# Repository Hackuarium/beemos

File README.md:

# BeeMoS - honey Bee Monitoring System<br/> (under development)

_[Lire en français](README.fr.md)_

The BeeMoS project is an open source bee hive monitoring system developed at the open science lab [Hackuarium](http://www.hackuarium.ch), Route de Crochy 20, Ecublens, Switzerland.

Please fee free to [contact us](https://form.jotformeu.com/71600609780354) if you would like more information.

# Objectives

Build and program an open source bee monitoring system capable of the following objectives:

- [x] Track the activity of the hives to study the behaviour of bees and monitor their health.
- [x] Track changes in the hive's weight over time to detect sudden and gradual changes (swarming, honey production ...).
- [x] Measures environmental variables including temperature, humidity, light and atmospheric pressure and study their effect on the bees.
- [ ] Send the data to a remote server for analysis, visualization or to notify the user if something unusual happens.

# Cloning the project

This project uses SUBMODULES

In order to clone use:

`git clone --recurse-submodules https://github.com/hackuarium/beemos`

To update the submodules, enter the folder you created ("beemos") and use:

`git submodule update --recursive --remote`

# Modules

To achieve the above objectives, the project follows a modular design with different hardware components. We use the I2C protocol to make modulles (i.e the boards) communicate to each other while using RJ-12 connectors in order to allow easy plugging/deplugging of different modules.

[**Counter**](counter-i2c/README.md): Counts bees entering and exiting the hive over time using infrared (IR) sensors. Each sensor consists in an IR emitter-receiver, the passage of a bee under the sensor modifies the reflected IR signal. A pair of IR sensors is used for each tunnel so that the direction of bees (i.e. entering or exiting the hive) can be determined.

Here is the orientation of the IR sensors at the back of the PCB. Be careful, the orientation of the Eagle file is seen from the top of the PCB.

[**Scale**](scale-i2c/README.md): Weighs the hive periodically using 4 load cells in Wheatstone bridge configuration.

[**Weather station**](weather-i2c/README.md): Monitors temperature, humidity, atmospheric pressure and luminosity outside of the hives.

[**Master board**](master/README.md): Communicates with all other devices over I2C, log data in memory and sends the data to a remote server. Can also track temperature inside the hive.

[**Simple master**](master-simple/README.md): A simple master board with I2C RJ-12 socket to
make some tests.

# State of the project

We have designed and ordered PCBs for the bee counter, weather station, scale and master boards. These four boards have been assembled and programmed. We also built a laser cut wooden enclosure which contains the bee counter PCB. It includes 8 individual gates that the bees use to enter/exit the hive and an upper compartment for the board so that sensor are on top of entering bees. A few field trials were launched to assess the accuracy of the bee counter but we still need to fix some things in the hardware and software to get it working (we detect false positives at the beginning and the end of sunny days, possibly due to sun beams entering and being counted as a passing bee). Similarly we need to further test the scale in order to confirm that measures are stable over long periods of time. 
Clara has joined the BeeMoS team in the summer of 2018 to make some tests of the bee counter in a controlled setting with live bees (transparent box with the beecounter inside and a camera to record video of entering/exiting bees that was compared to the readings from the board) and also participated in building a hive scale. 

The weather board can now show temperature, humidity, atmospheric pressure and relative light intensity. The scale board v1.0 has been soldered, a minor fix was needed to get it to work. The next steps will be to get the bee counter to work accurately by performing controlled tests, to assess the accuracy of the scale over time and to be able to send data wirelessly, integrate them to a database and plot them in an attractive way. 

We have assembled a complete kit, containing:
- 1 master board
- 1 counter board
- 1 scale board
- 1 weather board (to be protected from rain in a transparent container that lets the light through as well as an entry for the humidity to be accurately measured)
- 1 Si7021 humidity sensor
- 1 solar panel
- 2 temperature sensors (one wire DS18B20)
- 3 cables (RJ11 connectors)
- 1 battery 3.7V, 6600mA/h
- 1 wooden counter box
- 1 plastic box (to protect the master and scale boards from rain)
Here is what the kit actually looks like:

We already have assembled and tested some parts of it (the master, weight and weather boards in particular), but on an empty hive. The master board seems to log correctly and we are able to read the logs afterwards. Some things need to be fixed, for example sometimes the master board stops recording for long periods of time. It seems that this happens when the cables between boards (I2C interface) are too long. Since the 2G network will soon disappear in Switzerland, the SIM800L module will become useless (does not work with 3G and above). We are now (in October 2019) designing a new master board based on the ESP32 in order to be less limited in programming it (less memory limitations than for Atmega32u4-based boards) and also to have integrated WiFi and Bluetooth and possibly LoRa too for wireless communications. Since all the other boards are based on I2C communication, they should be easy to integrate with the new master board. Our current work related to ESP-32 can be found at https://github.com/Hackuarium/esp-32wroom (not tested yet).

# Further resources 

All codes, PCB board and schematic files and documentation can be found on the [BeeMoS github repository](https://github.com/Hackuarium/beemos) (in english only)

View this project on [CADLAB.io](https://cadlab.io/project/1029)

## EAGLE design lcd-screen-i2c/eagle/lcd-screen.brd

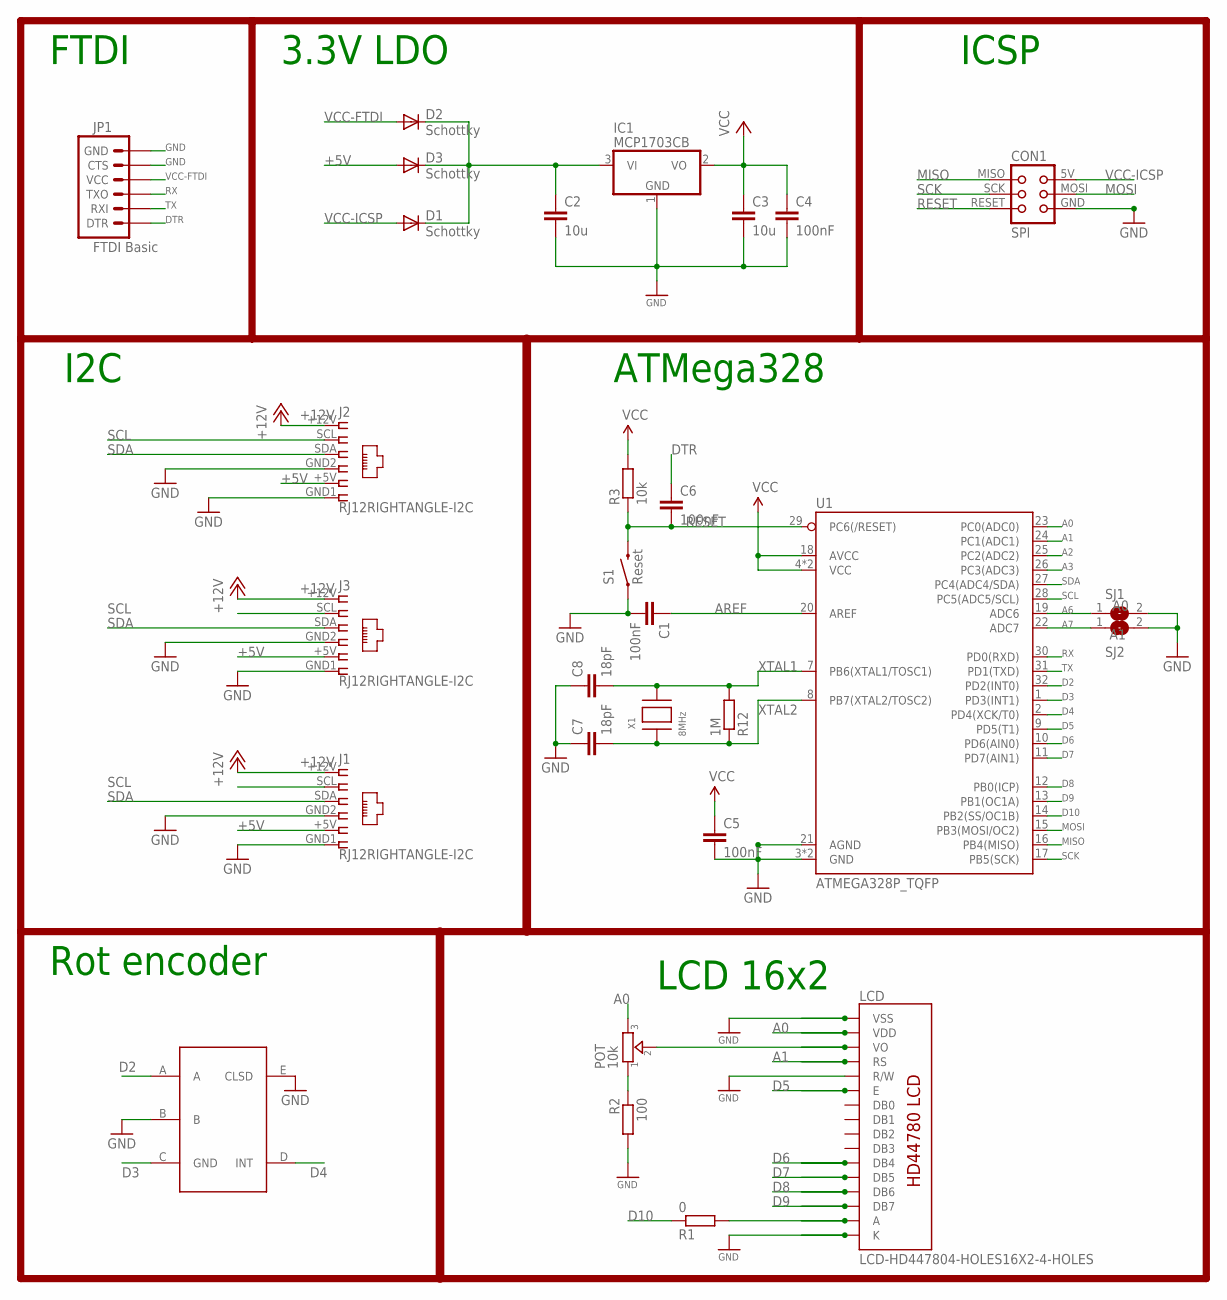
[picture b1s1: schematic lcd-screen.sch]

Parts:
C1, C4, C5, C6: 100nF; C0805K; MPN 80-C1206C104K5R; LCSC C49678
C2, C3: 10u; C0805K; MPN 77-VJ1206V106ZXQTBC; LCSC C15850
C7, C8: 18pF; C0805K; MPN 77-VJ1206A180JXXPBC; LCSC C1797
CON1: SPI; TC2030-MCP
D1, D2, D3: Schottky; SOD123; MPN 621-1N5819HW-F; LCSC C82544
IC1: MCP1703CB; SOT23; LCSC C53352
J1, J2, J3: RJ12RIGHTANGLE-I2C; RJ12-RIGHTANGLE-I2C
JP1: FTDI Basic; 1X06
LCD: LCD-HD447804-HOLES16X2-4-HOLES; LCD-16X2-4HOLES
POT: 10k; TRIMMER_3362P
R1: 0; R0805; LCSC C17477
R2: 100; R0805; LCSC C17408
R3: 10k; R0805; LCSC C17513
R12: 1M; R0805; LCSC C17514
S1: Reset; TACTILE-SWITCH-SMD-ALT01
SJ1: A0; SJ
SJ2: A1; SJ
U1: ATMEGA328P_TQFP; TQFP32-08
U$1: EC11E
X1: 8MHz; NX6035; MPN 729-F60800010; LCSC C122522

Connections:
+5V: D3.A, J1.+5V (5), J2.+5V (5), J3.+5V (5)
+12V: J1.+12V (1), J2.+12V (1), J3.+12V (1)
+XV: C2.1, D1.C, D2.C, D3.C, IC1.3 (VI)
A0: LCD.2 (VDD), POT.3, U1.23 (PC0(ADC0))
A1: LCD.4 (RS), U1.24 (PC1(ADC1))
A2: U1.25 (PC2(ADC2))
A3: U1.26 (PC3(ADC3))
A6: SJ1.1, U1.19 (ADC6)
A7: SJ2.1, U1.22 (ADC7)
AREF: C1.1, U1.20 (AREF)
D2: U1.32 (PD2(INT0)), U$1.A
D3: U1.1 (PD3(INT1)), U$1.C (GND)
D4: U1.2 (PD4(XCK/T0)), U$1.D (INT)
D5: LCD.6 (E), U1.9 (PD5(T1))
D6: LCD.11 (DB4), U1.10 (PD6(AIN0))
D7: LCD.12 (DB5), U1.11 (PD7(AIN1))
D8: LCD.13 (DB6), U1.12 (PB0(ICP))
D9: LCD.14 (DB7), U1.13 (PB1(OC1A))
D10: R1.1, U1.14 (PB2(SS/OC1B))
DTR: C6.1, JP1.1 (DTR)
GND: C1.2, C2.2, C3.2, C4.2, C5.2, C7.1, C8.1, CON1.GND, IC1.1 (GND), J1.GND1 (6), J1.GND2 (4), J2.GND1 (6), J2.GND2 (4), J3.GND1 (6), J3.GND2 (4), JP1.5 (CTS), JP1.6 (GND), LCD.1 (VSS), LCD.5 (R/W), LCD.16 (K), R2.2, S1.1, S1.2 (1), SJ1.2, SJ2.2, U1.3 (GND), U1.5 (GND), U1.21 (AGND), U$1.B, U$1.E (CLSD)
MISO: CON1.MISO, U1.16 (PB4(MISO))
MOSI: CON1.MOSI, U1.15 (PB3(MOSI/OC2))
unnamed: LCD.3 (VO), POT.2
unnamed: POT.1, R2.1
unnamed: LCD.15 (A), R1.2
RESET: C6.2, CON1.RESET, R3.1, S1.3 (2), S1.4 (2), U1.29 (PC6(/RESET))
RX: JP1.3 (TXO), U1.30 (PD0(RXD))
SCK: CON1.SCK, U1.17 (PB5(SCK))
SCL: J1.SCL (2), J2.SCL (2), J3.SCL (2), U1.28 (PC5(ADC5/SCL))
SDA: J1.SDA (3), J2.SDA (3), J3.SDA (3), U1.27 (PC4(ADC4/SDA))
TX: JP1.2 (RXI), U1.31 (PD1(TXD))
VCC: C3.1, C4.1, C5.1, IC1.2 (VO), R3.2, U1.4 (VCC), U1.6 (VCC), U1.18 (AVCC)
VCC-FTDI: D2.A, JP1.4 (VCC)
VCC-ICSP: CON1.5V (VCC), D1.A
XTAL1: C8.2, R12.2, U1.7 (PB6(XTAL1/TOSC1)), X1.P$2
XTAL2: C7.2, R12.1, U1.8 (PB7(XTAL2/TOSC2)), X1.P$1

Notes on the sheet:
ICSP
ATMega328
3.3V LDO
I2C
FTDI
LCD 16x2
Rot encoder

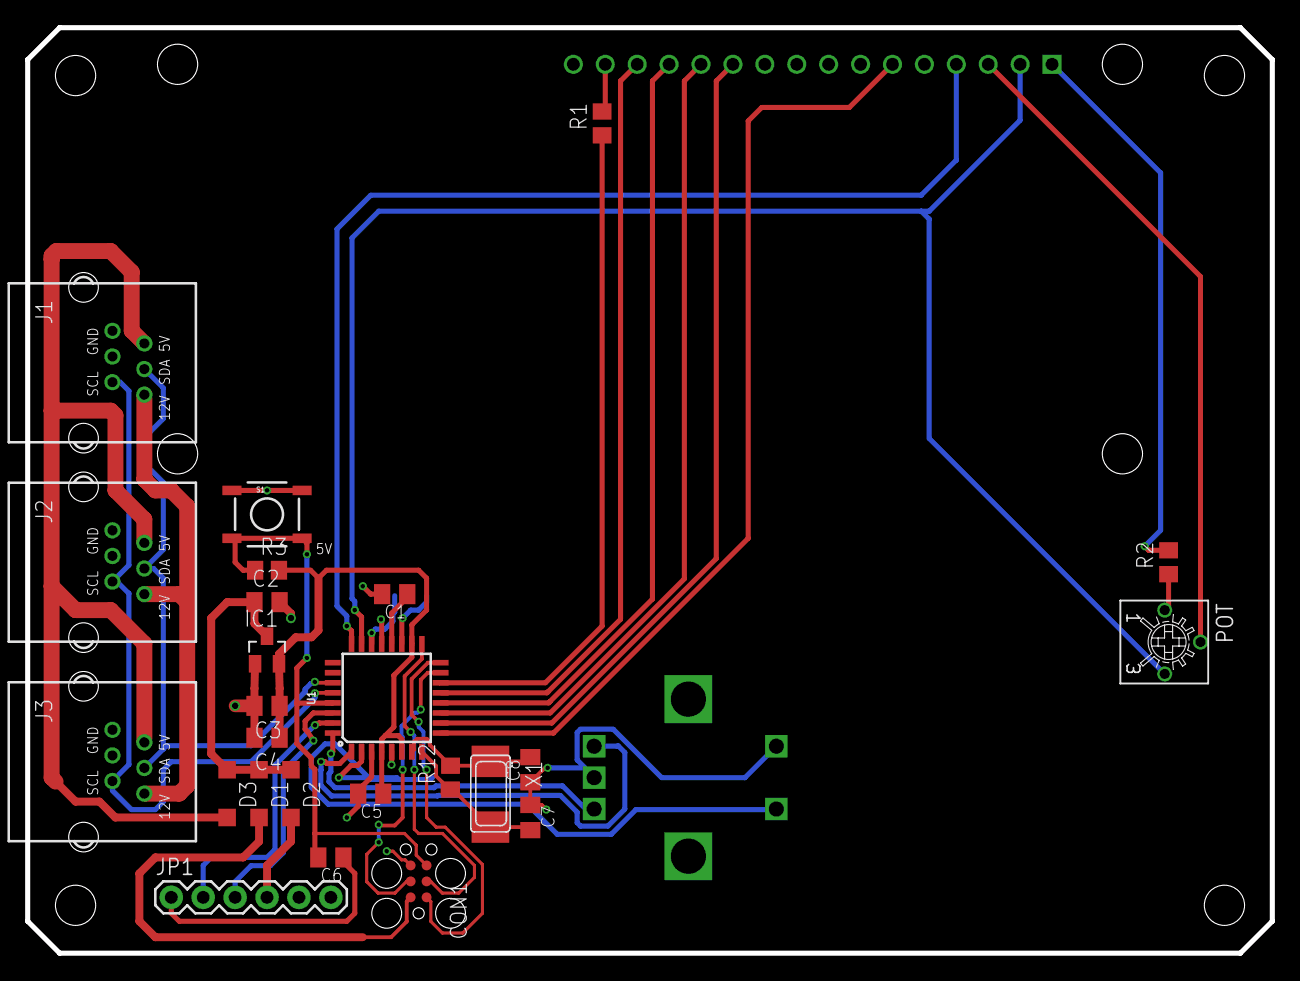
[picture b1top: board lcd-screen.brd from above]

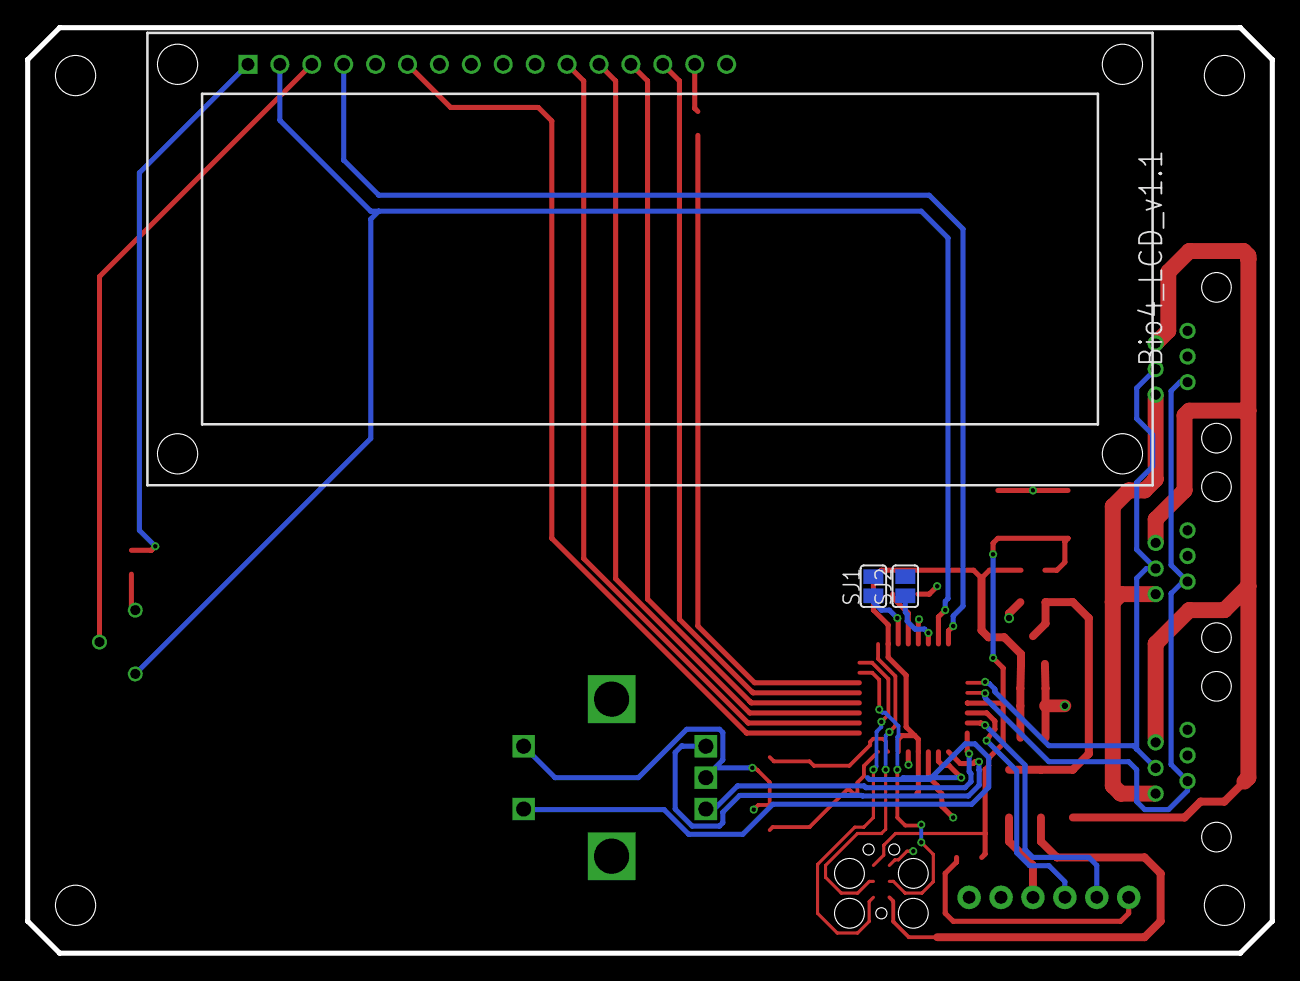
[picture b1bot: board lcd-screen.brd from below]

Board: 2 copper layers, 99.1 x 73.7 mm, 29 parts (4 on the bottom side), 35 nets.

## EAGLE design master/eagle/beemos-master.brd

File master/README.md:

## Master board

This board allows to connect SIM800L as well as I2C slaves.

It also has a flash memory of 64Kb.

### SIM800L

## Experiments

[August 14, 2018](docs/20180814/README.md)

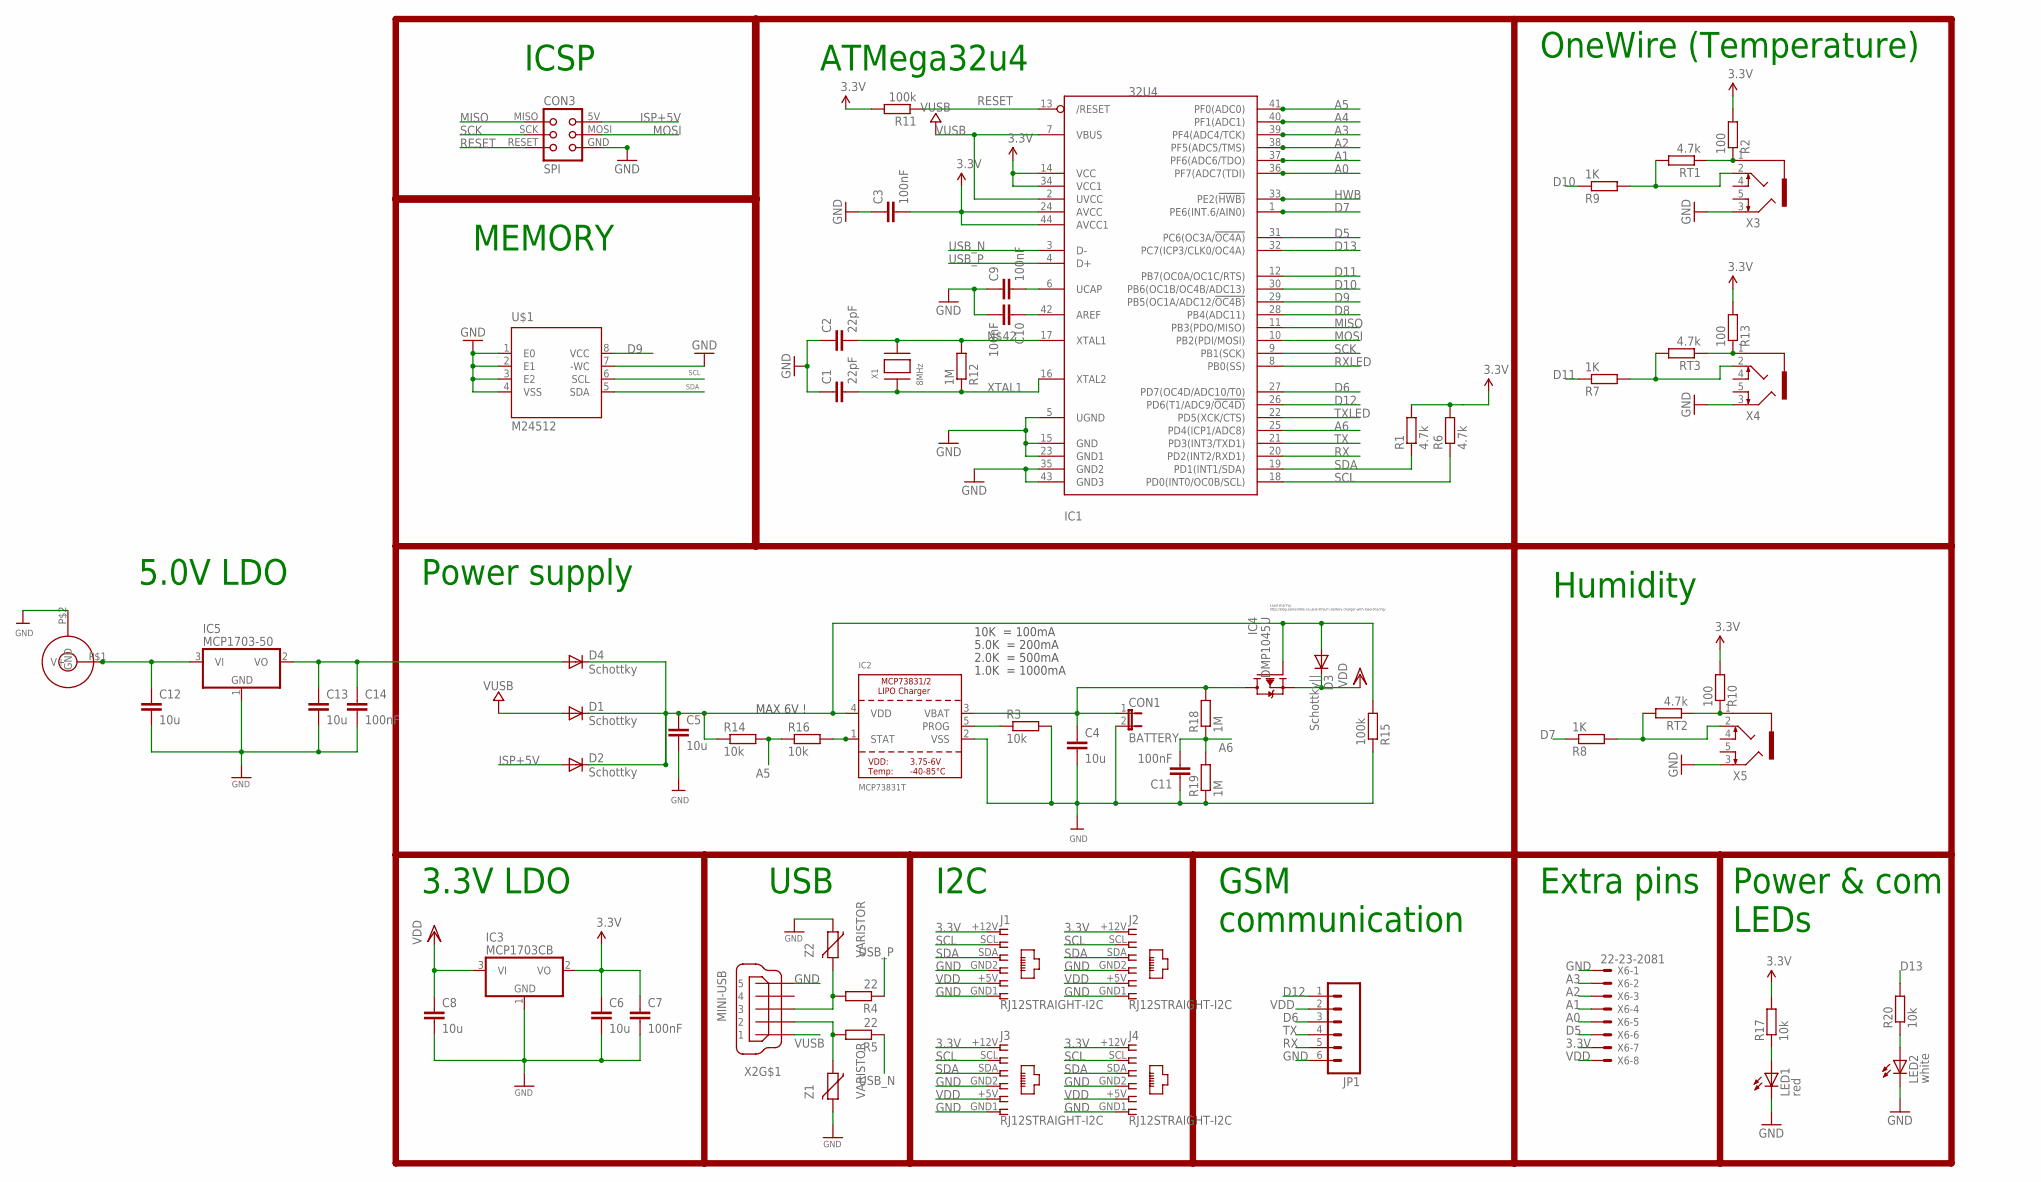
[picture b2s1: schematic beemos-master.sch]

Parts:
C1, C2: 22pF; C0805K; MPN 77-VJ1206A180JXXPBC; LCSC C1797
C3, C7, C9, C10, C11, C14: 100nF; C0805K; MPN 80-C1206C104K5R; LCSC C49678
C4, C5, C6, C8, C12, C13: 10u; C0805K; MPN 77-VJ1206V106ZXQTBC; LCSC C15850
CON1: BATTERY; JP1
CON2: JACK_DC_BARREL; DC_BARREL
CON3: SPI; TC2030-MCP-NL
D1, D2, D4: Schottky; SOD123; MPN 621-1N5819HW-F; LCSC C82544
D3: Schottky||; SOD123; MPN 621-1N5819HW-F; LCSC C82544
IC1: 32U4; TQFP44; MPN 556-ATMEGA32U4RC-AU; LCSC C44854
IC2: MCP73831T; SOT23-5; MPN 579-MCP73831T-3ACIOT; LCSC C14879
IC3: MCP1703CB; SOT23; LCSC C53352
IC4: DMP1045U; SOT-23; MPN 621-DMP1045U-7; LCSC C96613
IC5: MCP1703-50; SOT23
J1, J2, J3, J4: RJ12STRAIGHT-I2C; RJ12-STRAIGHT-I2C
JP1: M06RA; MOLEX-1X6-RA
LED1: red; CHIP-LED0805
LED2: white; CHIP-LED0805
R1, R6: 4.7k; R0805
R2, R10, R13: 100; R0805
R3: 10k; R0805; LCSC C17414
R4, R5: 22; R0805; LCSC C17561
R7, R8, R9: 1K; R0805
R11, R15: 100k; R0805; MPN RC1206FR-07100KL; LCSC C17407
R12, R18, R19: 1M; R0805; LCSC C17514
R14, R16: 10k; R0805; LCSC C17513
R17, R20: 10k; R0805
RT1, RT2, RT3: 4.7k; R0805
U$1: M24512; SO8
X1: 8MHz; NX6035; MPN 729-F60800010; LCSC C122522
X2: MINI-USB; 32005-201; MPN 649-10033526-N3212LF; LCSC C46391
X3, X4, X5: 1503_09
X6: 22-23-2081
Z1, Z2: VARISTOR; CT/CN0805; LCSC C79709

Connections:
3.3V: C3.2, C6.1, C7.1, IC1.14 (VCC), IC1.24 (AVCC), IC1.34 (VCC1), IC1.44 (AVCC1), IC3.2 (VO), J1.+12V (1), J2.+12V (1), J3.+12V (1), J4.+12V (1), R1.2, R2.2, R6.2, R10.2, R11.2, R13.2, R17.2, X6.7
A0: IC1.36 (PF7(ADC7(TDI)), X6.5
A1: IC1.37 (PF6(ADC6/TDO)), X6.4
A2: IC1.38 (PF5(ADC5/TMS)), X6.3
A3: IC1.39 (PF4(ADC4/TCK)), X6.2
A4: IC1.40 (PF1(ADC1))
A5: IC1.41 (PF0(ADC0)), R14.2, R16.1
A6: C11.2, IC1.25 (PD4(ICP1/ADC8)), R18.1, R19.2
AREF: C10.1, IC1.42 (AREF)
D5: IC1.31 (PC6(OC3A/!OC4A)), X6.6
D6: IC1.27 (PD7(OC4D/ADC10/T0)), JP1.3
D7: IC1.1 (PE6(INT.6/AIN0)), R8.1
D8: IC1.28 (PB4(ADC11))
D9: IC1.29 (PB5(OC1A/ADC12/!OC4B)), U$1.8 (VCC)
D10: IC1.30 (PB6(OC1B/OC4B/ADC13)), R9.1
D11: IC1.12 (PB7(OC0A/OC1C/RTS)), R7.1
D12: IC1.26 (PD6(T1/ADC9/!OC4D)), JP1.1
D13: IC1.32 (PC7(ICP3/CLK0/OC4A)), R20.2
GND: C1.1, C2.1, C3.1, C4.2, C5.2, C6.2, C7.2, C8.2, C9.1, C10.2, C11.1, C12.2, C13.2, C14.2, CON1.2, CON2.P$2 (GND), CON3.GND, IC1.5 (UGND), IC1.15 (GND), IC1.23 (GND1), IC1.35 (GND2), IC1.43 (GND3), IC2.2 (VSS), IC3.1 (GND), IC5.1 (GND), J1.GND1 (6), J1.GND2 (4), J2.GND1 (6), J2.GND2 (4), J3.GND1 (6), J3.GND2 (4), J4.GND1 (6), J4.GND2 (4), JP1.6, LED1.C, LED2.C, R3.2, R15.1, R19.1, U$1.1 (E0), U$1.2 (E1), U$1.3 (E2), U$1.4 (VSS), U$1.7 (-WC), X2.5, X3.3, X4.3, X5.3, X6.1, Z1.2, Z2.1
HWB: IC1.33 (PE2(!HWB))
ISP+5V: CON3.5V (VCC), D2.A
MISO: CON3.MISO, IC1.11 (PB3(PDO/MISO))
MOSI: CON3.MOSI, IC1.10 (PB2(PDI/MOSI))
unnamed: C9.2, IC1.6 (UCAP)
unnamed: R7.2, RT3.2, X4.2
unnamed: C13.1, C14.1, D4.A, IC5.2 (VO)
unnamed: R13.1, RT3.1, X4.1
unnamed: C5.1, D1.C, D2.C, D3.A, D4.C, IC2.4 (VDD), IC4.1 (G), R14.1, R15.2
unnamed: IC2.5 (PROG), R3.1
unnamed: IC2.1 (STAT), R16.2
unnamed: R8.2, RT2.2, X5.2
unnamed: R10.1, RT2.1, X5.1
unnamed: LED1.A, R17.1
unnamed: LED2.A, R20.1
unnamed: C12.1, CON2.P$1 (V+), IC5.3 (VI)
unnamed: R2.1, RT1.1, X3.1
unnamed: R9.2, RT1.2, X3.2
unnamed: C2.2, IC1.17 (XTAL1), R12.2, X1.P$2
RESET: CON3.RESET, IC1.13 (/RESET), R11.1
RX: IC1.20 (PD2(INT2/RXD1)), JP1.5
RXLED: IC1.8 (PB0(SS))
SCK: CON3.SCK, IC1.9 (PB1(SCK))
SCL: IC1.18 (PD0(INT0/OC0B/SCL)), J1.SCL (2), J2.SCL (2), J3.SCL (2), J4.SCL (2), R6.1, U$1.6 (SCL)
SDA: IC1.19 (PD1(INT1/SDA)), J1.SDA (3), J2.SDA (3), J3.SDA (3), J4.SDA (3), R1.1, U$1.5 (SDA)
TX: IC1.21 (PD3(INT3/TXD1)), JP1.4
TXLED: IC1.22 (PD5(XCK/CTS))
USBC_N: R5.2, X2.2, Z1.1
USBC_P: R4.2, X2.3, Z2.2
USB_N: IC1.3 (D-), R5.1
USB_P: IC1.4 (D+), R4.1
VBAT1: C4.1, CON1.1, IC2.3 (VBAT), IC4.3 (D), R18.2
VDD: C8.1, D3.C, IC3.3 (VI), IC4.2 (S), J1.+5V (5), J2.+5V (5), J3.+5V (5), J4.+5V (5), JP1.2, X6.8
VUSB: D1.A, IC1.2 (UVCC), IC1.7 (VBUS), X2.1
XTAL1: C1.2, IC1.16 (XTAL2), R12.1, X1.P$1

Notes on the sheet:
USB
ICSP
ATMega32u4
3.3V LDO
10K = 100mA
5.0K = 200mA
2.0K = 500mA
1.0K = 1000mA
MAX 6V !
Load sharing: http://blog.zakkemble.co.uk/a-lithium-battery-charger-with-load-sharing/
I2C
Power supply
OneWire (Temperature)
MEMORY
GSM communication
Humidity
Extra pins
Power & com LEDs
5.0V LDO

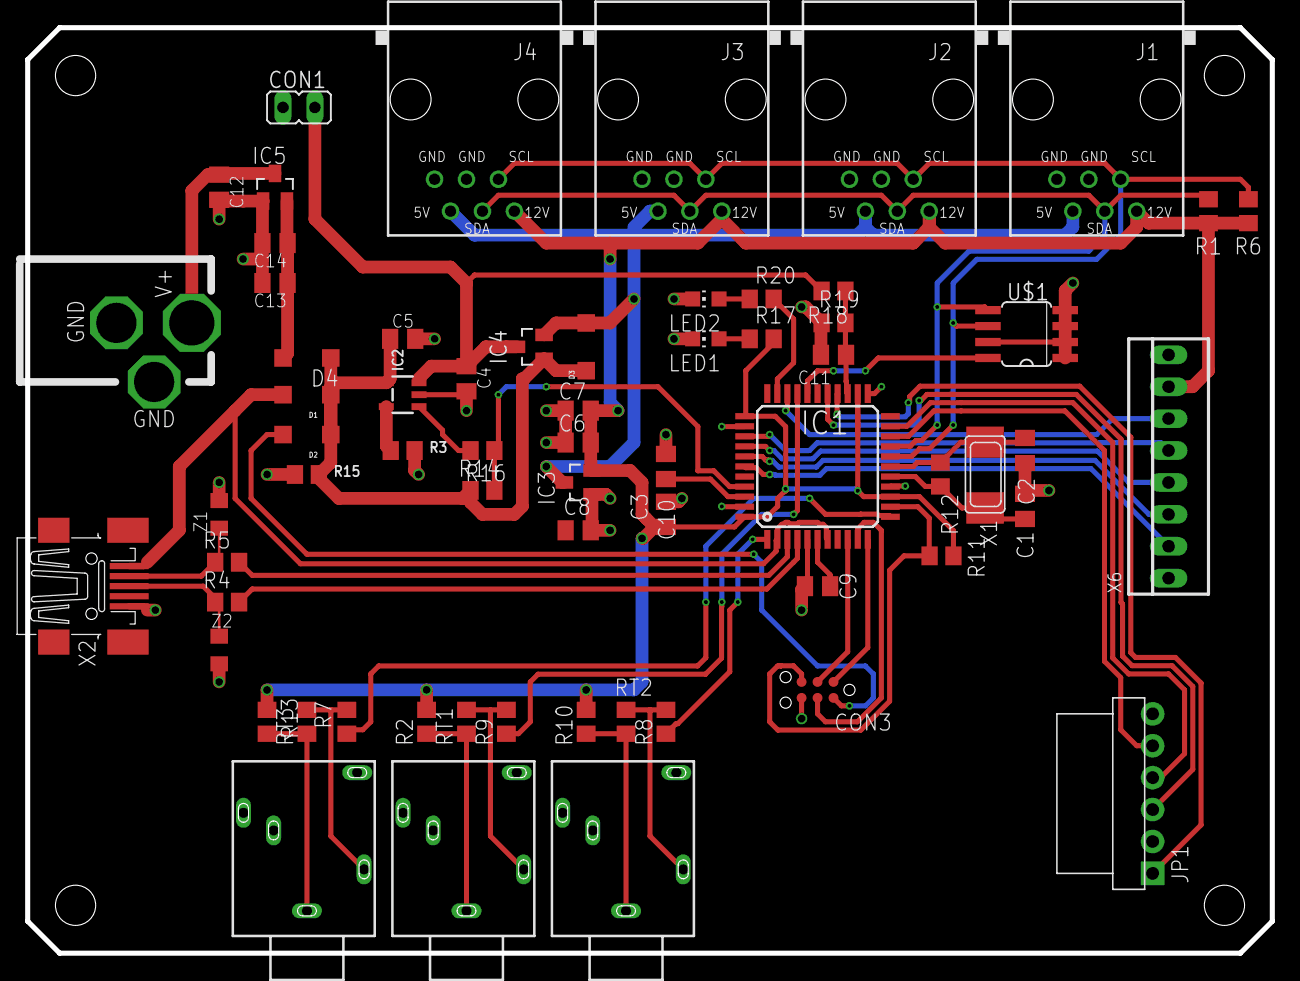
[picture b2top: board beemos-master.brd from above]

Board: 2 copper layers, 99.1 x 73.7 mm, 65 parts (0 on the bottom side), 49 nets.

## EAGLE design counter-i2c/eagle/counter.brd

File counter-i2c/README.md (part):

Bee-counter i2c

<p align="right">

</p>

# Bee-counter i2c

Using an Arduino based microcontroller, infrared (= IR) reflectance sensors are used to detect if a bee is present under the sensor, thereby modifying the reflected IR signal read by the microcontroller. Each gate consists of two IR reflectance sensors, each capable of emitting and receiving an IR signal. This allows to determine whether the bee is entering or exiting the hive by looking at which of the two sensors reacted first to the presence of the bee below it.

## Components

- x1 Microprocessor Atmel 32u4 (similar to Arduino Leonardo boards), 8Mhz, 3.3V
- x16 QRE1113 IR reflectance sensors (x2 per gate)
- x1 74HC154W demultiplexer used to switch on the IR led of one of the 16 IR reflectance sensors
- x1 74HC4067 multiplexer used to read the value from one of the IR reflectance sensors (the one which has the IR led on)

## Performances

Scanning all 16 IR sensors: 3ms
Current consumption: 27mA

## The box

The box consists in a laser cut wooden enclosure, which contains the bee counter PCB. It includes 8 individual gates that the bees use to enter/exit the hive and an upper compartment for the board so that sensor are on top of entering bees.

## Parameters

There are 26 parameters:

| ID  | Name                   | Description                                                                          |
| --- | ---------------------- | ------------------------------------------------------------------------------------ |
| 0   | PARAM_LOGID            | the log ID                                                                           |
| 1   | PARAM_SECONDS          | the number of seconds since the last log                                             |
| 2   | PARAM_GATE1_IN         | gate 1 counter of events IN                                                          |
| 3   | PARAM_GATE1_OUT        | gate 1 counter of events OUT                                                         |
| 4   | PARAM_GATE2_IN         | gate 2 counter of events IN                                                          |
| 5   | PARAM_GATE2_OUT        | gate 2 counter of events OUT                                                         |
| 6   | PARAM_GATE3_IN         | gate 3 counter of events IN                                                          |
| 7   | PARAM_GATE3_OUT        | gate 3 counter of events OUT                                                         |
| 8   | PARAM_GATE4_IN         | gate 4 counter of events IN                                                          |
| 9   | PARAM_GATE4_OUT        | gate 4 counter of events OUT                                                         |
| 10  | PARAM_GATE5_IN         | gate 5 counter of events IN                                                          |
| 11  | PARAM_GATE5_OUT        | gate 5 counter of events OUT                                                         |
| 12  | PARAM_GATE6_IN         | gate 6 counter of events IN                                                          |
| 13  | PARAM_GATE6_OUT        | gate 6 counter of events OUT                                                         |
| 14  | PARAM_GATE7_IN         | gate 7 counter of events IN                                                          |
| 15  | PARAM_GATE7_OUT        | gate 7 counter of events OUT                                                         |
| 16  | PARAM_GATE8_IN         | gate 8 counter of events IN                                                          |
| 17  | PARAM_GATE8_OUT        | gate 8 counter of events OUT                                                         |
| 20  | PARAM_THRESHOLD        | the threshold of absorbance to reach to conclude there is a bee crossing the gate    |
| 21  | PARAM_THRESHOLD_RESET  | the threshold of absorbance to conclude that the event is finished                   |
| 22  | PARAM_DEBUG_REPEAT     | the duration of the gate debug monitoring                                            |
| 23  | PARAM_DEBUG_DELAY      | the delay between two successive displays of debug information                       |
| 24  | PARAM_LOGGING_INTERVAL | the time interval between two logs (should be at least 300s)                         |
| 25  | PARAM_DEBUG_PRINT      | a boolean to enable the debug mode. `Z1` allows to enable debug, `Z0` to disable it. |

## Menu and commands

Here is the actual menu, accessible by typing "h" + enter.

- (h)elp
- (s)ettings
- (u)tilities
- (b)ackground
- (c)ounter
- (g)ate debug bg
- (l)og

`Settings` gives access to the current values of the settings. To change the value of a setting, just type the letter of the setting (A-Z) and the new value of the setting in the chat box and press enter.
`Gate debug mode` activates the real-time monitoring system. Each time a bee pass through a tunnel, the time, the number of the gate, the absorbance values of the two sensors and the number of bees outside is displayed.

## When do we have an event ?

The system will calculate the background which is the value of the receiver when no bee is in the gate.
In order to evaluate this background, the last 15 values of each detector and the background will
be the median of those values.

An event will start when the change observe to a detector is larger than `PARAM_THRESHOLD`. This event
will finish when this value will go under ``PARAM_THRESHOLD_RESET`.

In order to well detect an event it would make sense that the value of ** the background is between
96 and 160 **. A low value means that the receiver receives too much IR. We could ensure that the voltage
is really 3.3v and if it is the case we could think about a high resistor value for the IR led.

You can easily check the background values using the option `b`.

## Gate validation (tested with USB and MCP1703-50)

In order to validate the board it is practical to use a Q-tip and to use the `gate debug bg`
menu item (`g`).

This mode will check for absolute value variation compared to the background value.
If this variation is over the `PARAM_THRESHOLD` the value will be displayed. The measurements are done
and display the value`PARAM_DEBUG_REPEAT` times and separated by `PARAM_DEBUG_DELAY` (500, which means 500 ms,
is a good value).

With a Q-tip we should detect a variation for the "in" and "out" detector of each gate.

In the following logs we can see that the Gate 1 and 3 have problems because both event are not detected.

```
Gate 1 - Inside: 2  - Outside: 39
Gate 1 - Inside: 3  - Outside: 38
Gate 1 - Inside: 3  - Outside: 33
Gate 1 - Inside: 0  - Outside: 13
Gate 1 - Inside: 1  - Outside: 24
Gate 1 - Inside: 3  - Outside: 36
Gate 1 - Inside: 3  - Outside: 38
Gate 1 - Inside: 0  - Outside: 17
Gate 2 - Inside: 1  - Outside: 5
Gate 2 - Inside: 11 - Outside: 12
Gate 2 - Inside: 13 - Outside: 11
Gate 2 - Inside: 14 - Outside: 11
Gate 2 - Inside: 14 - Outside: 11
Gate 2 - Inside: 12 - Outside: 12
Gate 3 - Inside: 11 - Outside: 2
Gate 3 - Inside: 10 - Outside: 2
Gate 3 - Inside: 10 - Outside: 1
Gate 3 - Inside: 10 - Outside: 2
Gate 4 - Inside: 7  - Outside: 12
Gate 4 - Inside: 6  - Outside: 10
Gate 4 - Inside: 6  - Outside: 11
Gate 4 - Inside: 8  - Outside: 11
Gate 4 - Inside: 2  - Outside: 7
```

If we look at the background values (`b`) we obtain:

```
0 19 19 19 19 19 19 19 19 19 19 19 19 19 19 19 25
1 3B 3B 3C 3C 3C 3C 3C 3C 3C 3C 3C 3C 3C 3C 3C 60
2 23 23 23 23 23 23 23 23 23 23 23 23 23 23 23 35
3 20 1F 20 20 20 20 20 20 20 20 20 20 20 20 20 32
4 22 22 22 22 22 22 21 22 22 22 22 22 22 22 21 34
5 18 18 17 17 18 17 18 17 17 17 18 17 18 17 17 23
6 1D 1D 1D 1D 1D 1D 1D 1D 1D 1D 1D 1D 1D 1D 1D 29
7 20 20 20 20 20 20 20 20 20 20 20 20 20 20 20 32
8 3B 3B 3B 3B 3B 3B 3B 3B 3B 3B 3B 3B 3B 3B 3B 59
9 1A 1A 1A 1A 1A 1A 1A 1A 1A 1A 1A 1A 1A 1A 1A 26
10 29 29 29 29 29 29 29 29 29 29 29 29 29 29 29 41
11 20 20 21 21 21 21 21 21 21 21 21 21 21 21 21 33
12 23 23 23 23 23 23 23 23 23 23 23 23 23 23 23 35
13 27 27 27 27 27 27 27 27 27 27 27 27 28 27 27 39
14 2D 2C 2C 2D 2C 2D 2D 2D 2D 2D 2D 2D 2C 2D 2C 45
15 1B 1B 1B 1B 1B 1C 1B 1B 1C 1B 1B 1B 1B 1B 1B 27
```

The variation between the values are huge and the origin is currently unknown.

## Studying the background (MCP1703-50)

Conditions:

- power supply is USB
- convert is MCP1703-50 !!! (5v) so the voltage should be close to 4.7 !

We did various tests to get the average value depending the surface and the distance. In order
to make the measurement we use a very simple setup in which we control the distance between the
PCB and the surface.

| Surface     | Distance [mm] | Value | SD    |
| ----------- | ------------- | ----- | ----- |
| Black wood  | 2             | 157   | 16.51 |
| Black wood  | 4.5           | 234   | 2.94  |
| Black wood  | 5.3           | 239   | 3.32  |
| Black wood  | 6             | 245   | 3.32  |
| Black wood  | 8.5           | 249   | 3.86  |
| Black wood  | 10            | 250   | 4.96  |
| Black wood  | 12            | 251   | 5.59  |
| MDF         | 2             | 18    | 0.50  |
| MDF         | 4.5           | 20    | 0.62  |
| MDF         | 5.3           | 21    | 0.48  |
| MDF         | 6             | 26    | 7.84  |
| MDF         | 8.5           | 104   | 14.38 |
| MDF         | 10            | 144   | 9.58  |
| MDF         | 12            | 169   | 12.44 |
| White paper | 2             | 18    | 0.45  |
| White paper | 4.5           | 20    | 0.50  |
| White paper | 5.3           | 22    | 0.45  |
| White paper | 6             | 26    | 4.27  |
| White paper | 8.5           | 119   | 19.22 |
| White paper | 10            | 141   | 10.87 |
| White paper | 12            | 182   | 11.61 |

We observe that it is barely possible to measure anything on black surface. MDF or white
paper is ok but the distance is critical.

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
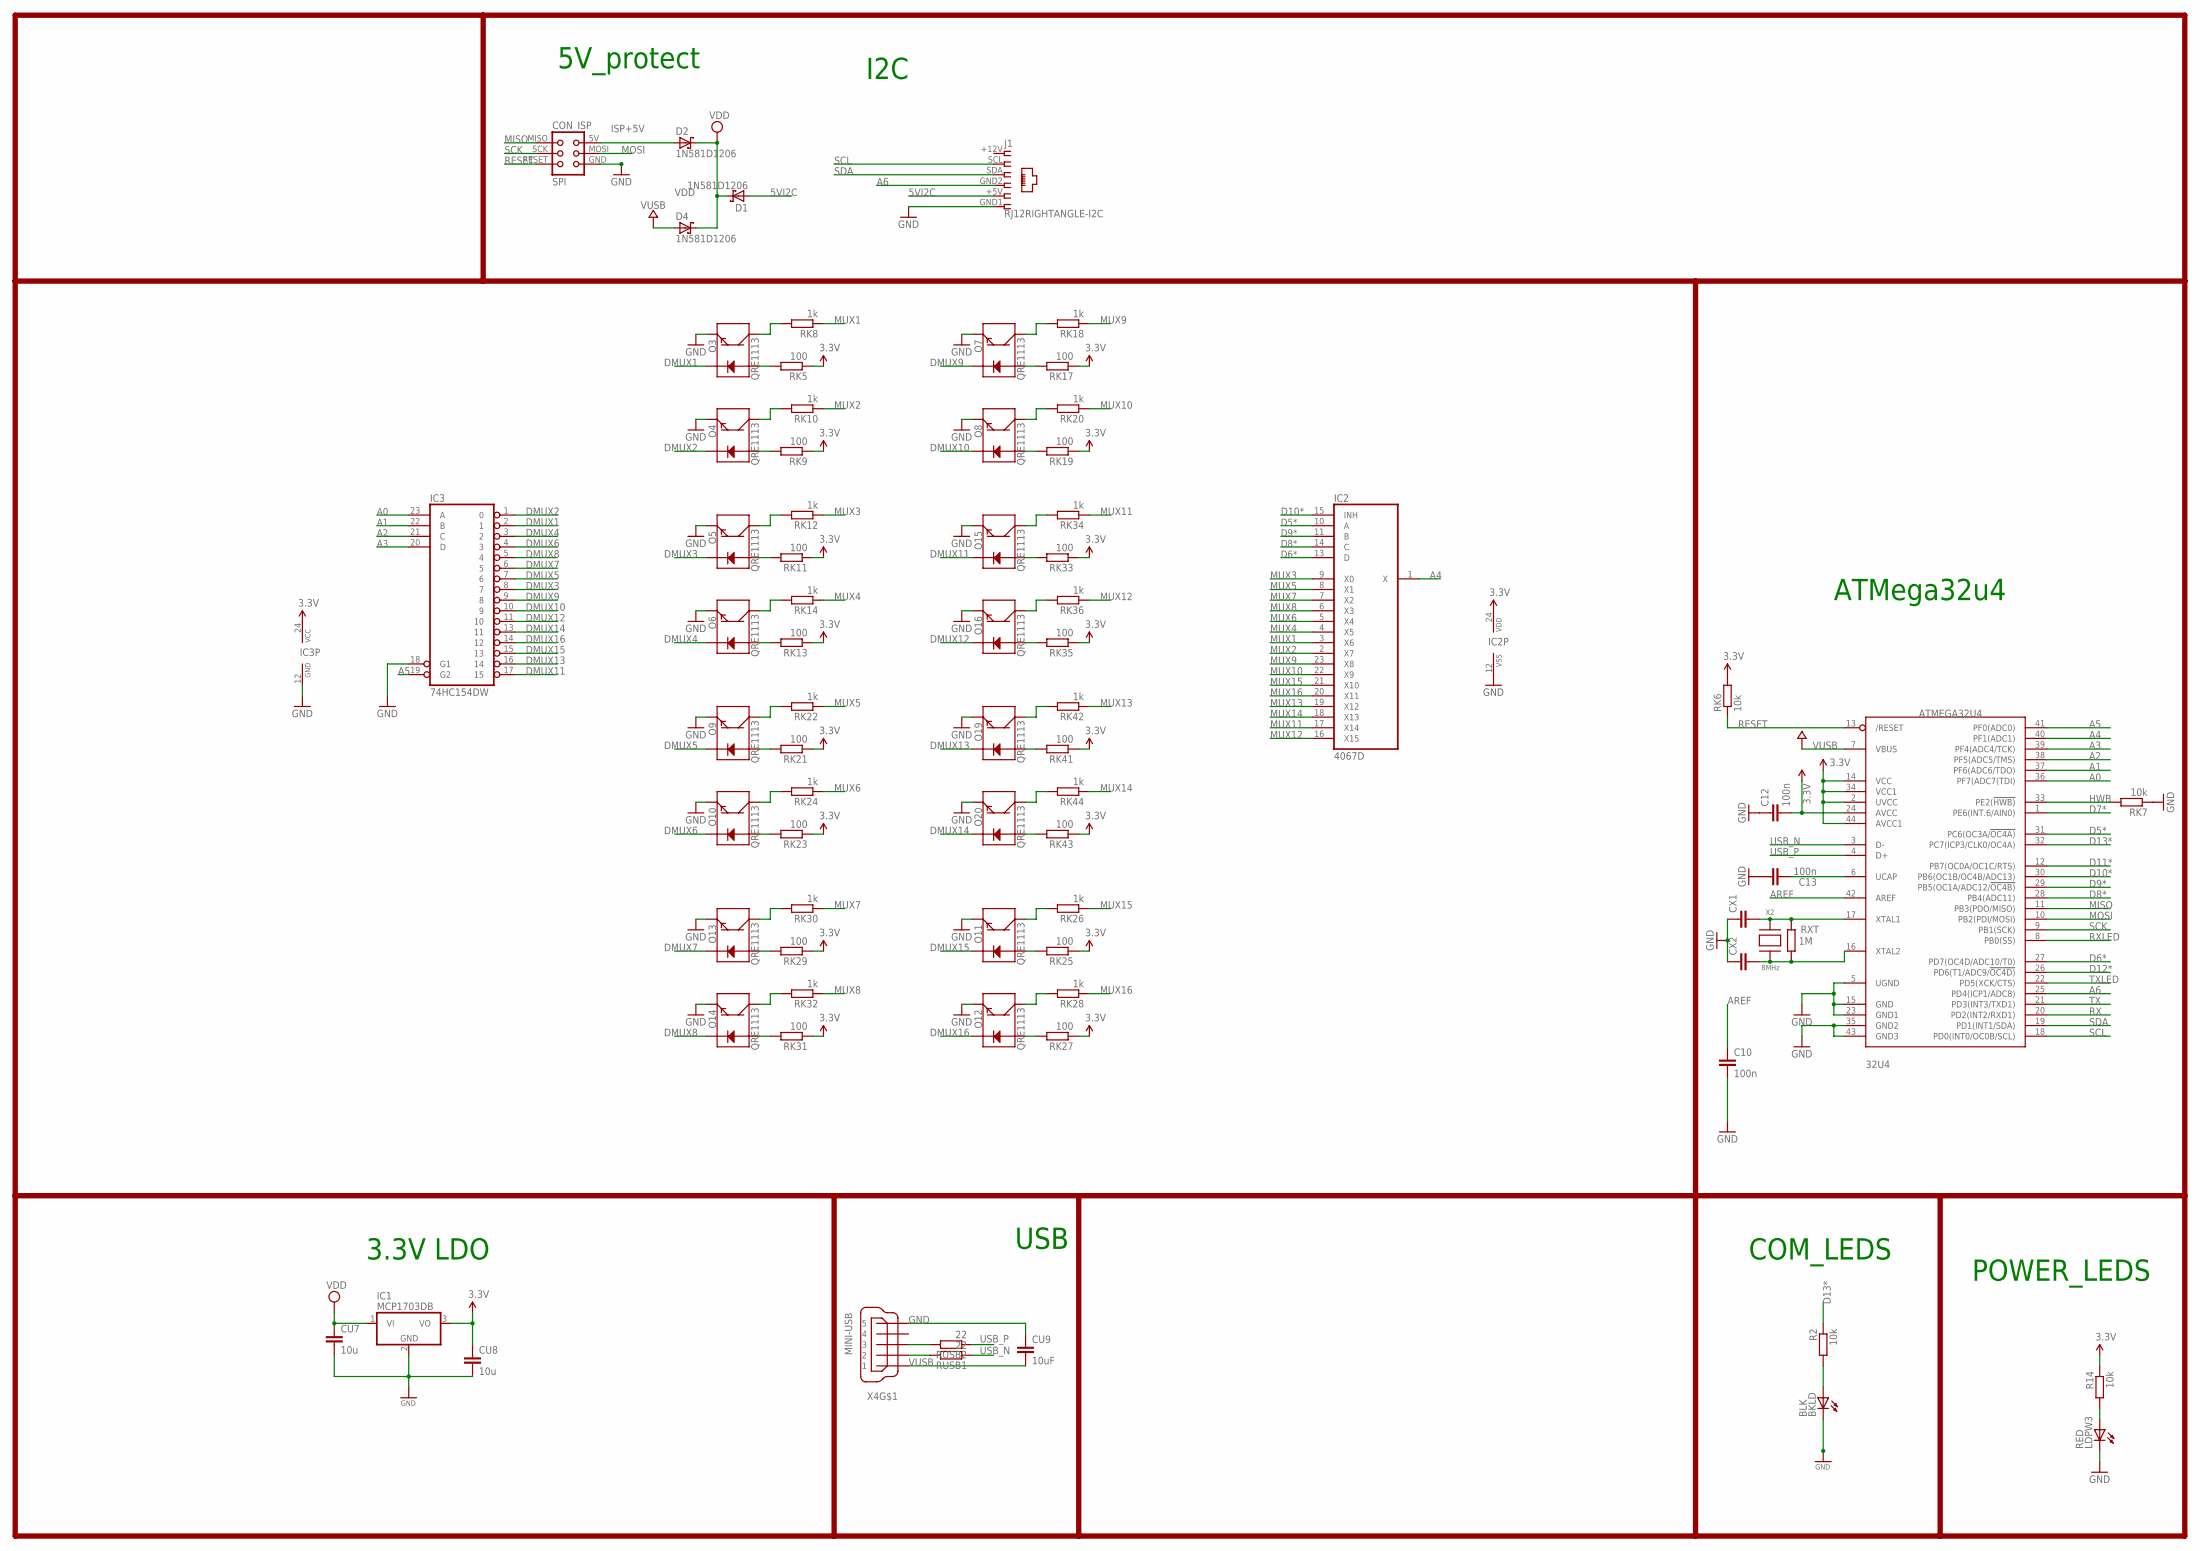
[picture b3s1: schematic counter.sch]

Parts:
32U4: ATMEGA32U4; TQFP44
BKLD: BLK; CHIP-LED0805
C10, C12, C13: 100n; C0805
CON_ISP: SPI; TC2030-MCP-NL
CU7, CU8: 10u; C0805
CU9: 10uF; C0805
CX1, CX2: 22pF; C0805
D1, D2, D4: 1N581D1206; LED-1206
IC1: MCP1703DB; SOT223
IC2: 4067D; SO24W
IC3: 74HC154DW; SO24W
J1: RJ12RIGHTANGLE-I2C; RJ12-RIGHTANGLE-I2C
LDPW3: RED; CHIP-LED0805
O3, O4, O5, O6, O7, O8, O9, O10, O11, O12, O13, O14, O15, O16, O19, O20: QRE1113
R2, R14: 10k; R0805
RK5, RK9, RK11, RK13, RK17, RK19, RK21, RK23, RK25, RK27, RK29, RK31, RK33, RK35, RK41, RK43: 100; M0805
RK6, RK7: 10k; M0805
RK8, RK10, RK12, RK14, RK18, RK20, RK22, RK24, RK26, RK28, RK30, RK32, RK34, RK36, RK42, RK44: 1k; M0805
RUSB1, RUSB2: 22; M0805
RXT: 1M; R0805
X2: 8MHz; NX6035
X4: MINI-USB; 32005-201

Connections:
1: J1.+12V (1)
3.3V: 32U4.2 (UVCC), 32U4.14 (VCC), 32U4.24 (AVCC), 32U4.34 (VCC1), 32U4.44 (AVCC1), C12.2, CU8.1, IC1.3 (VO), IC2.24 (VDD), IC3.24 (VCC), R14.1, RK5.1, RK6.2, RK9.1, RK11.1, RK13.1, RK17.1, RK19.1, RK21.1, RK23.1, RK25.1, RK27.1, RK29.1, RK31.1, RK33.1, RK35.1, RK41.1, RK43.1
5VI2C: D1.A, J1.+5V (5)
A0: 32U4.36 (PF7(ADC7(TDI)), IC3.23 (A)
A1: 32U4.37 (PF6(ADC6/TDO)), IC3.22 (B)
A2: 32U4.38 (PF5(ADC5/TMS)), IC3.21 (C)
A3: 32U4.39 (PF4(ADC4/TCK)), IC3.20 (D)
A4: 32U4.40 (PF1(ADC1)), IC2.1 (X)
A5: 32U4.41 (PF0(ADC0)), IC3.19 (G2)
A6: 32U4.25 (PD4(ICP1/ADC8)), J1.GND2 (4)
AREF: 32U4.42 (AREF), C10.1
D5*: 32U4.31 (PC6(OC3A/!OC4A)), IC2.10 (A)
D6*: 32U4.27 (PD7(OC4D/ADC10/T0)), IC2.13 (D)
D7*: 32U4.1 (PE6(INT.6/AIN0))
D8*: 32U4.28 (PB4(ADC11)), IC2.14 (C)
D9*: 32U4.29 (PB5(OC1A/ADC12/!OC4B)), IC2.11 (B)
D10*: 32U4.30 (PB6(OC1B/OC4B/ADC13)), IC2.15 (INH)
D11*: 32U4.12 (PB7(OC0A/OC1C/RTS))
D12*: 32U4.26 (PD6(T1/ADC9/!OC4D))
D13*: 32U4.32 (PC7(ICP3/CLK0/OC4A)), R2.1
DMUX1: IC3.2 (1), O3.2 (K)
DMUX2: IC3.1 (0), O4.2 (K)
DMUX3: IC3.8 (7), O5.2 (K)
DMUX4: IC3.3 (2), O6.2 (K)
DMUX5: IC3.7 (6), O9.2 (K)
DMUX6: IC3.4 (3), O10.2 (K)
DMUX7: IC3.6 (5), O13.2 (K)
DMUX8: IC3.5 (4), O14.2 (K)
DMUX9: IC3.9 (8), O7.2 (K)
DMUX10: IC3.10 (9), O8.2 (K)
DMUX11: IC3.17 (15), O15.2 (K)
DMUX12: IC3.11 (10), O16.2 (K)
DMUX13: IC3.16 (14), O19.2 (K)
DMUX14: IC3.13 (11), O20.2 (K)
DMUX15: IC3.15 (13), O11.2 (K)
DMUX16: IC3.14 (12), O12.2 (K)
GND: 32U4.5 (UGND), 32U4.15 (GND), 32U4.23 (GND1), 32U4.35 (GND2), 32U4.43 (GND3), BKLD.C, C10.2, C12.1, C13.1, CON_ISP.GND, CU7.2, CU8.2, CU9.1, CX1.1, CX2.1, IC1.2 (GND), IC2.12 (VSS), IC3.12 (GND), IC3.18 (G1), J1.GND1 (6), LDPW3.C, O3.4 (E), O4.4 (E), O5.4 (E), O6.4 (E), O7.4 (E), O8.4 (E), O9.4 (E), O10.4 (E), O11.4 (E), O12.4 (E), O13.4 (E), O14.4 (E), O15.4 (E), O16.4 (E), O19.4 (E), O20.4 (E), RK7.1, X4.5
HWB: 32U4.33 (PE2(!HWB)), RK7.2
ISP+5V: CON_ISP.5V (VCC), D2.A
MISO: 32U4.11 (PB3(PDO/MISO)), CON_ISP.MISO
MOSI: 32U4.10 (PB2(PDI/MOSI)), CON_ISP.MOSI
MUX1: IC2.3 (X6), RK8.1
MUX2: IC2.2 (X7), RK10.1
MUX3: IC2.9 (X0), RK12.1
MUX4: IC2.4 (X5), RK14.1
MUX5: IC2.8 (X1), RK22.1
MUX6: IC2.5 (X4), RK24.1
MUX7: IC2.7 (X2), RK30.1
MUX8: IC2.6 (X3), RK32.1
MUX9: IC2.23 (X8), RK18.1
MUX10: IC2.22 (X9), RK20.1
MUX11: IC2.17 (X14), RK34.1
MUX12: IC2.16 (X15), RK36.1
MUX13: IC2.19 (X12), RK42.1
MUX14: IC2.18 (X13), RK44.1
MUX15: IC2.21 (X10), RK26.1
MUX16: IC2.20 (X11), RK28.1
unnamed: 32U4.6 (UCAP), C13.2
unnamed: BKLD.A, R2.2
unnamed: LDPW3.A, R14.2
unnamed: 32U4.17 (XTAL1), CX1.2, RXT.2, X2.P$2
RD3: O3.1 (A), RK5.2
RD4: O4.1 (A), RK9.2
RD5: O5.1 (A), RK11.2
RD6: O6.1 (A), RK13.2
RD7: O7.1 (A), RK17.2
RD8: O8.1 (A), RK19.2
RD9: O9.1 (A), RK21.2
RD10: O10.1 (A), RK23.2
RD11: O11.1 (A), RK25.2
RD12: O12.1 (A), RK27.2
RD13: O13.1 (A), RK29.2
RD14: O14.1 (A), RK31.2
RD15: O15.1 (A), RK33.2
RD16: O16.1 (A), RK35.2
RD19: O19.1 (A), RK41.2
RD20: O20.1 (A), RK43.2
RESET: 32U4.13 (/RESET), CON_ISP.RESET, RK6.1
RX: 32U4.20 (PD2(INT2/RXD1))
RXLED: 32U4.8 (PB0(SS))
SCK: 32U4.9 (PB1(SCK)), CON_ISP.SCK
SCL: 32U4.18 (PD0(INT0/OC0B/SCL)), J1.SCL (2)
SDA: 32U4.19 (PD1(INT1/SDA)), J1.SDA (3)
TX: 32U4.21 (PD3(INT3/TXD1))
TXLED: 32U4.22 (PD5(XCK/CTS))
USBC_N: RUSB1.2, X4.2
USBC_P: RUSB2.2, X4.3
USB_N: 32U4.3 (D-), RUSB1.1
USB_P: 32U4.4 (D+), RUSB2.1
VDD: CU7.1, D1.C, D2.C, D4.C, IC1.1 (VI)
VUSB: 32U4.7 (VBUS), CU9.2, D4.A, X4.1
XTAL1: 32U4.16 (XTAL2), CX2.2, RXT.1, X2.P$1
Y3: O3.3 (C), RK8.2
Y4: O4.3 (C), RK10.2
Y5: O5.3 (C), RK12.2
Y6: O6.3 (C), RK14.2
Y7: O7.3 (C), RK18.2
Y8: O8.3 (C), RK20.2
Y9: O9.3 (C), RK22.2
Y10: O10.3 (C), RK24.2
Y11: O11.3 (C), RK26.2
Y12: O12.3 (C), RK28.2
Y13: O13.3 (C), RK30.2
Y14: O14.3 (C), RK32.2
Y15: O15.3 (C), RK34.2
Y16: O16.3 (C), RK36.2
Y19: O19.3 (C), RK42.2
Y20: O20.3 (C), RK44.2

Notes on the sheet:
USB
I2C
5V_protect
POWER_LEDS
COM_LEDS
3.3V LDO
ATMega32u4

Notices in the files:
parts and their libraries:
lpatiny: ©2009 ROFA.cz - modified and updated by Robert Darlington ‹rdarlington@gmail.com›
SparkFun: Licensing: CC v3.0 Share-Alike You are welcome to use this library for commercial purposes.
